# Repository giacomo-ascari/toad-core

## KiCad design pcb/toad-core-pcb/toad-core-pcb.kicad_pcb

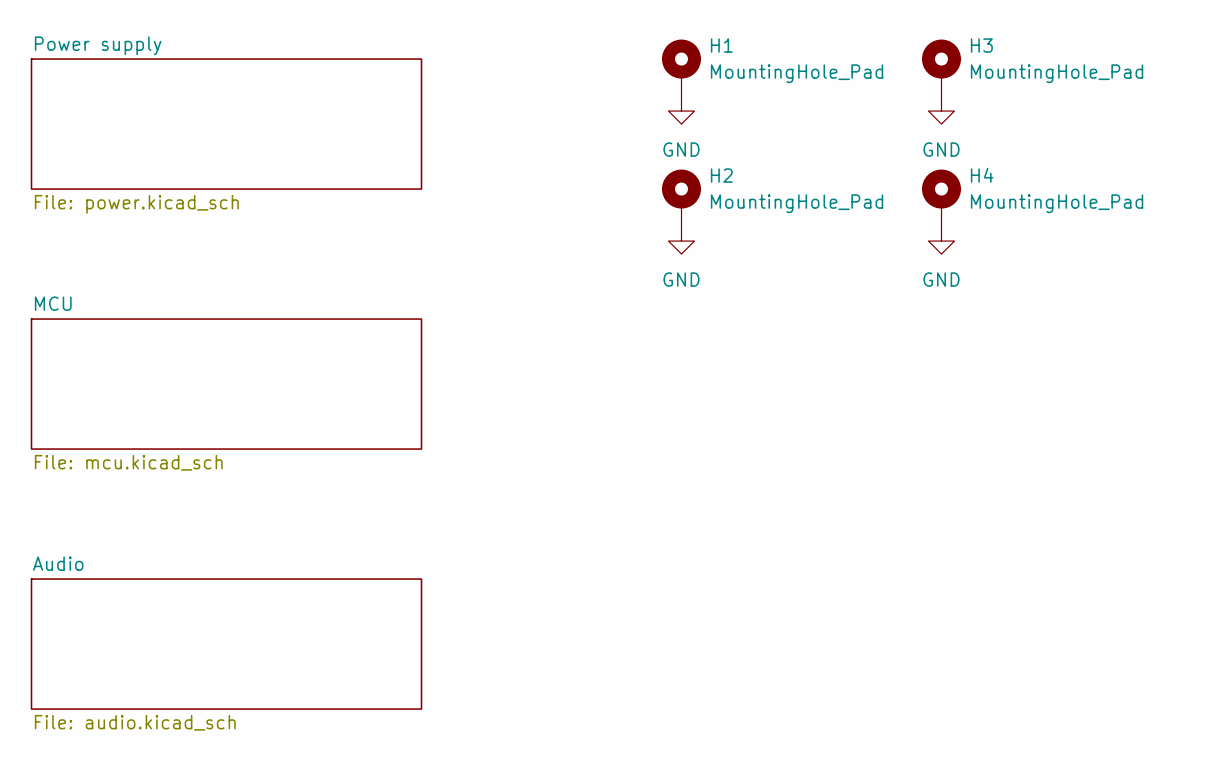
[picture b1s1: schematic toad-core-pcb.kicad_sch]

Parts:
H1, H2, H3, H4: MountingHole_Pad; MountingHole_3.2mm_M3_ISO14580_Pad

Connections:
GND: H1.1 (1_1), H2.1 (1_1), H3.1 (1_1), H4.1 (1_1); also elsewhere on the board

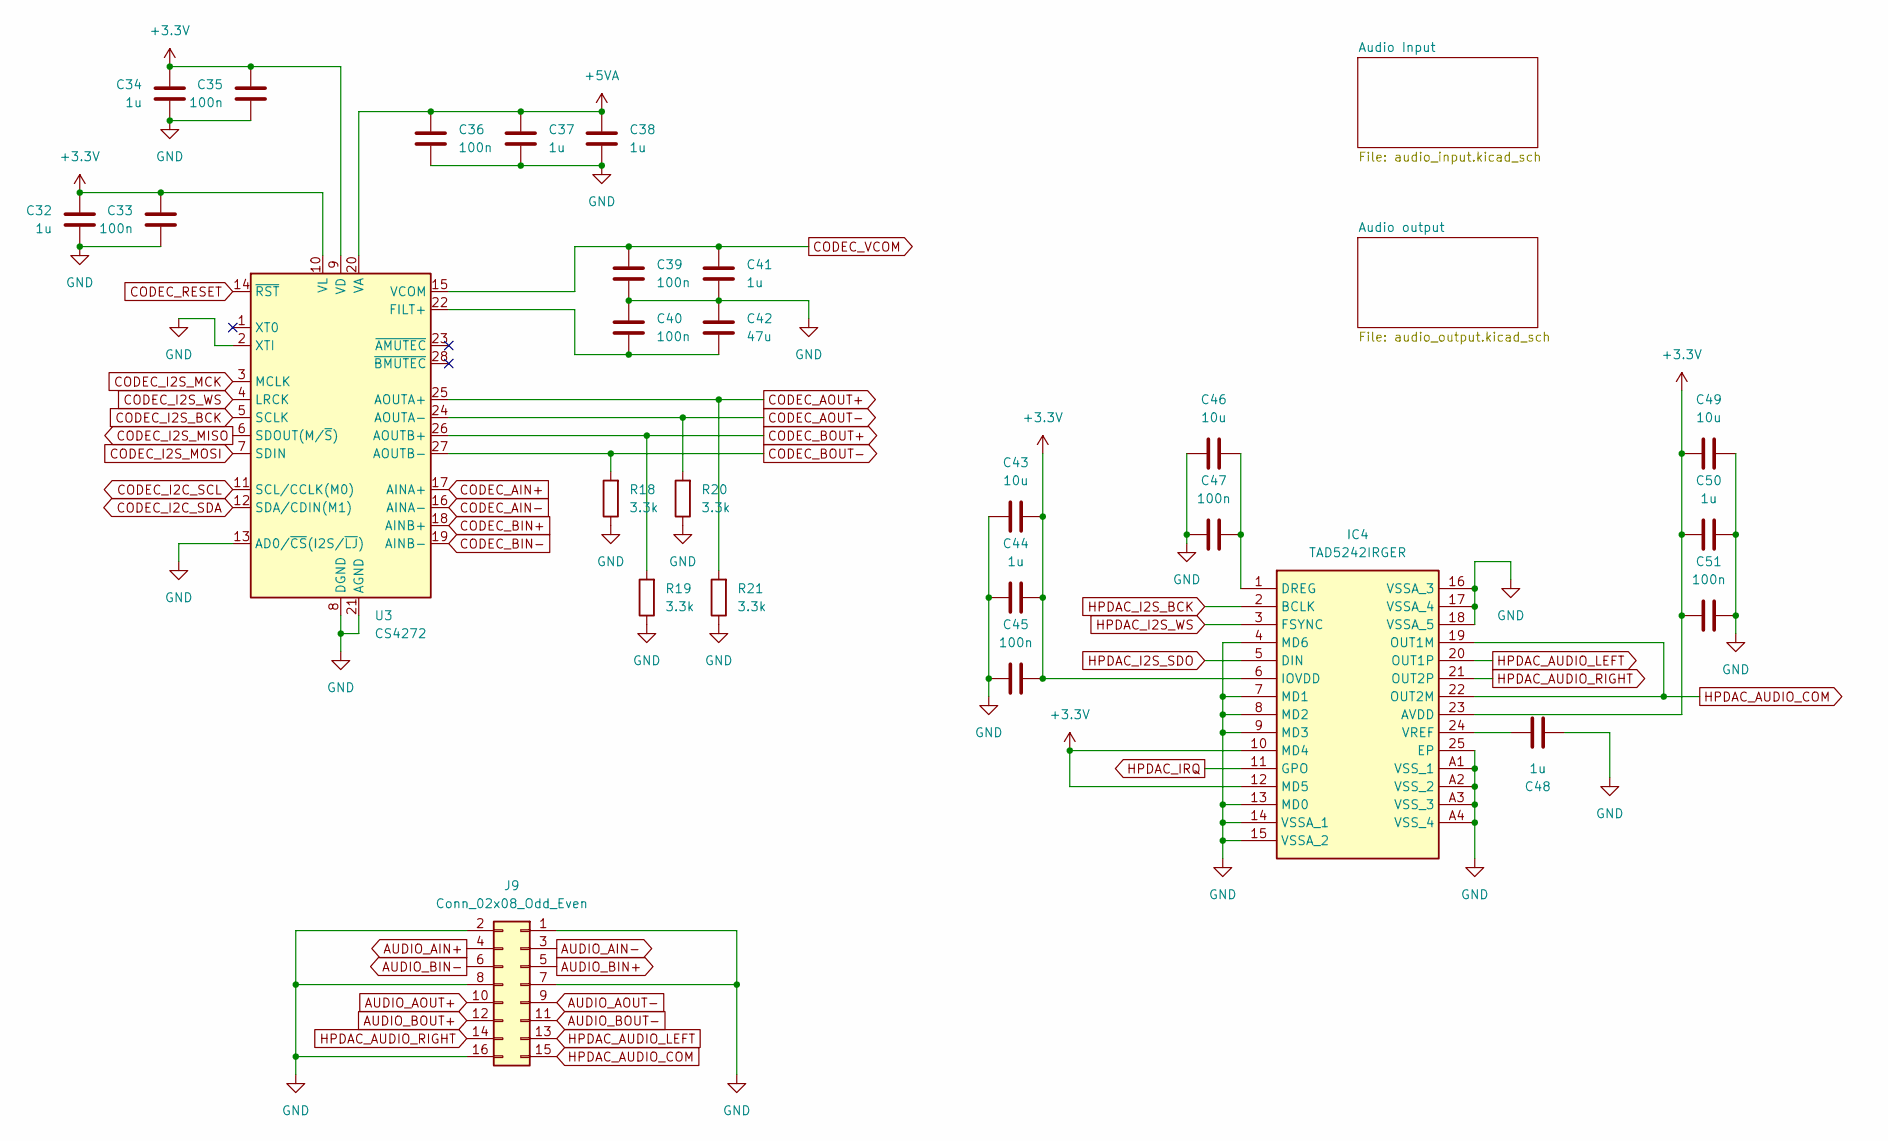
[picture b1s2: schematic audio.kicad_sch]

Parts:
C32, C34, C37, C38, C41, C44, C48, C50: 1u; C_0603_1608Metric
C33, C35, C36, C39, C40, C45, C47, C51: 100n; C_0603_1608Metric
C42: 47u; C_0805_2012Metric
C43, C46, C49: 10u; C_0805_2012Metric
IC4: TAD5242IRGER; Manufacturer_Part_Number TAD5242IRGER; Mouser Part Number 595-TAD5242IRGER
J9: Conn_02x08_Odd_Even; PinHeader_2x08_P2.54mm_Vertical
R18, R19, R20, R21: 3.3k; R_0603_1608Metric
U3: CS4272; TSSOP-28_4.4x9.7mm_P0.65mm

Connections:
+3.3V: C32.1, C33.1, C34.1, C35.1, C43.1, C44.1, C45.1, C49.1, C50.1, C51.1, IC4.6 (IOVDD), IC4.10 (MD4), IC4.12 (MD5), IC4.23 (AVDD), U3.9 (VD), U3.10 (VL); also elsewhere on the board
+5VA: C36.1, C37.1, C38.1, U3.20 (VA); also elsewhere on the board
AUDIO_AIN+: J9.4; also elsewhere on the board
AUDIO_AIN-: J9.3; also elsewhere on the board
AUDIO_AOUT+: J9.10; also elsewhere on the board
AUDIO_AOUT-: J9.9; also elsewhere on the board
AUDIO_BIN+: J9.5; also elsewhere on the board
AUDIO_BIN-: J9.6; also elsewhere on the board
AUDIO_BOUT+: J9.12; also elsewhere on the board
AUDIO_BOUT-: J9.11; also elsewhere on the board
CODEC_AIN+: U3.17 (AINA+); also elsewhere on the board
CODEC_AIN-: U3.16 (AINA-); also elsewhere on the board
CODEC_AOUT+: R21.2, U3.25 (AOUTA+); also elsewhere on the board
CODEC_AOUT-: R20.2, U3.24 (AOUTA-); also elsewhere on the board
CODEC_BIN+: U3.18 (AINB+); also elsewhere on the board
CODEC_BIN-: U3.19 (AINB-); also elsewhere on the board
CODEC_BOUT+: R19.2, U3.26 (AOUTB+); also elsewhere on the board
CODEC_BOUT-: R18.2, U3.27 (AOUTB-); also elsewhere on the board
CODEC_I2C_SCL: U3.11 (SCL/CCLK(M0)); also elsewhere on the board
CODEC_I2C_SDA: U3.12 (SDA/CDIN(M1)); also elsewhere on the board
CODEC_I2S_BCK: U3.5 (SCLK); also elsewhere on the board
CODEC_I2S_MCK: U3.3 (MCLK); also elsewhere on the board
CODEC_I2S_MISO: U3.6 (SDOUT(M/~S)); also elsewhere on the board
CODEC_I2S_MOSI: U3.7 (SDIN); also elsewhere on the board
CODEC_I2S_WS: U3.4 (LRCK); also elsewhere on the board
CODEC_RESET: U3.14 (~RST); also elsewhere on the board
CODEC_VCOM: C39.1, C41.1, U3.15 (VCOM); also elsewhere on the board
GND: C32.2, C33.2, C34.2, C35.2, C36.2, C37.2, C38.2, C39.2, C40.1, C41.2, C42.1, C43.2, C44.2, C45.2, C46.2, C47.2, C48.1, C49.2, C50.2, C51.2, IC4.4 (MD6), IC4.7 (MD1), IC4.8 (MD2), IC4.9 (MD3), IC4.13 (MD0), IC4.14 (VSSA_1), IC4.15 (VSSA_2), IC4.16 (VSSA_3), IC4.17 (VSSA_4), IC4.18 (VSSA_5), IC4.25 (EP), IC4.A1 (VSS_1), IC4.A2 (VSS_2), IC4.A3 (VSS_3), IC4.A4 (VSS_4), J9.1, J9.2, J9.7, J9.8, J9.16, R18.1, R19.1, R20.1, R21.1, U3.2 (XTI), U3.8 (DGND), U3.13 (AD0/~CS(I2S/~LJ)), U3.21 (AGND); also elsewhere on the board
HPDAC_AUDIO_COM: IC4.19 (OUT1M), IC4.22 (OUT2M), J9.15
HPDAC_AUDIO_LEFT: IC4.20 (OUT1P), J9.13
HPDAC_AUDIO_RIGHT: IC4.21 (OUT2P), J9.14
HPDAC_I2S_BCK: IC4.2 (BCLK); also elsewhere on the board
HPDAC_I2S_SDO: IC4.5 (DIN); also elsewhere on the board
HPDAC_I2S_WS: IC4.3 (FSYNC); also elsewhere on the board
HPDAC_IRQ: IC4.11 (GPO); also elsewhere on the board
unnamed: C46.1, C47.1, IC4.1 (DREG)
unnamed: C48.2, IC4.24 (VREF)
unnamed: C40.2, C42.2, U3.22 (FILT+)

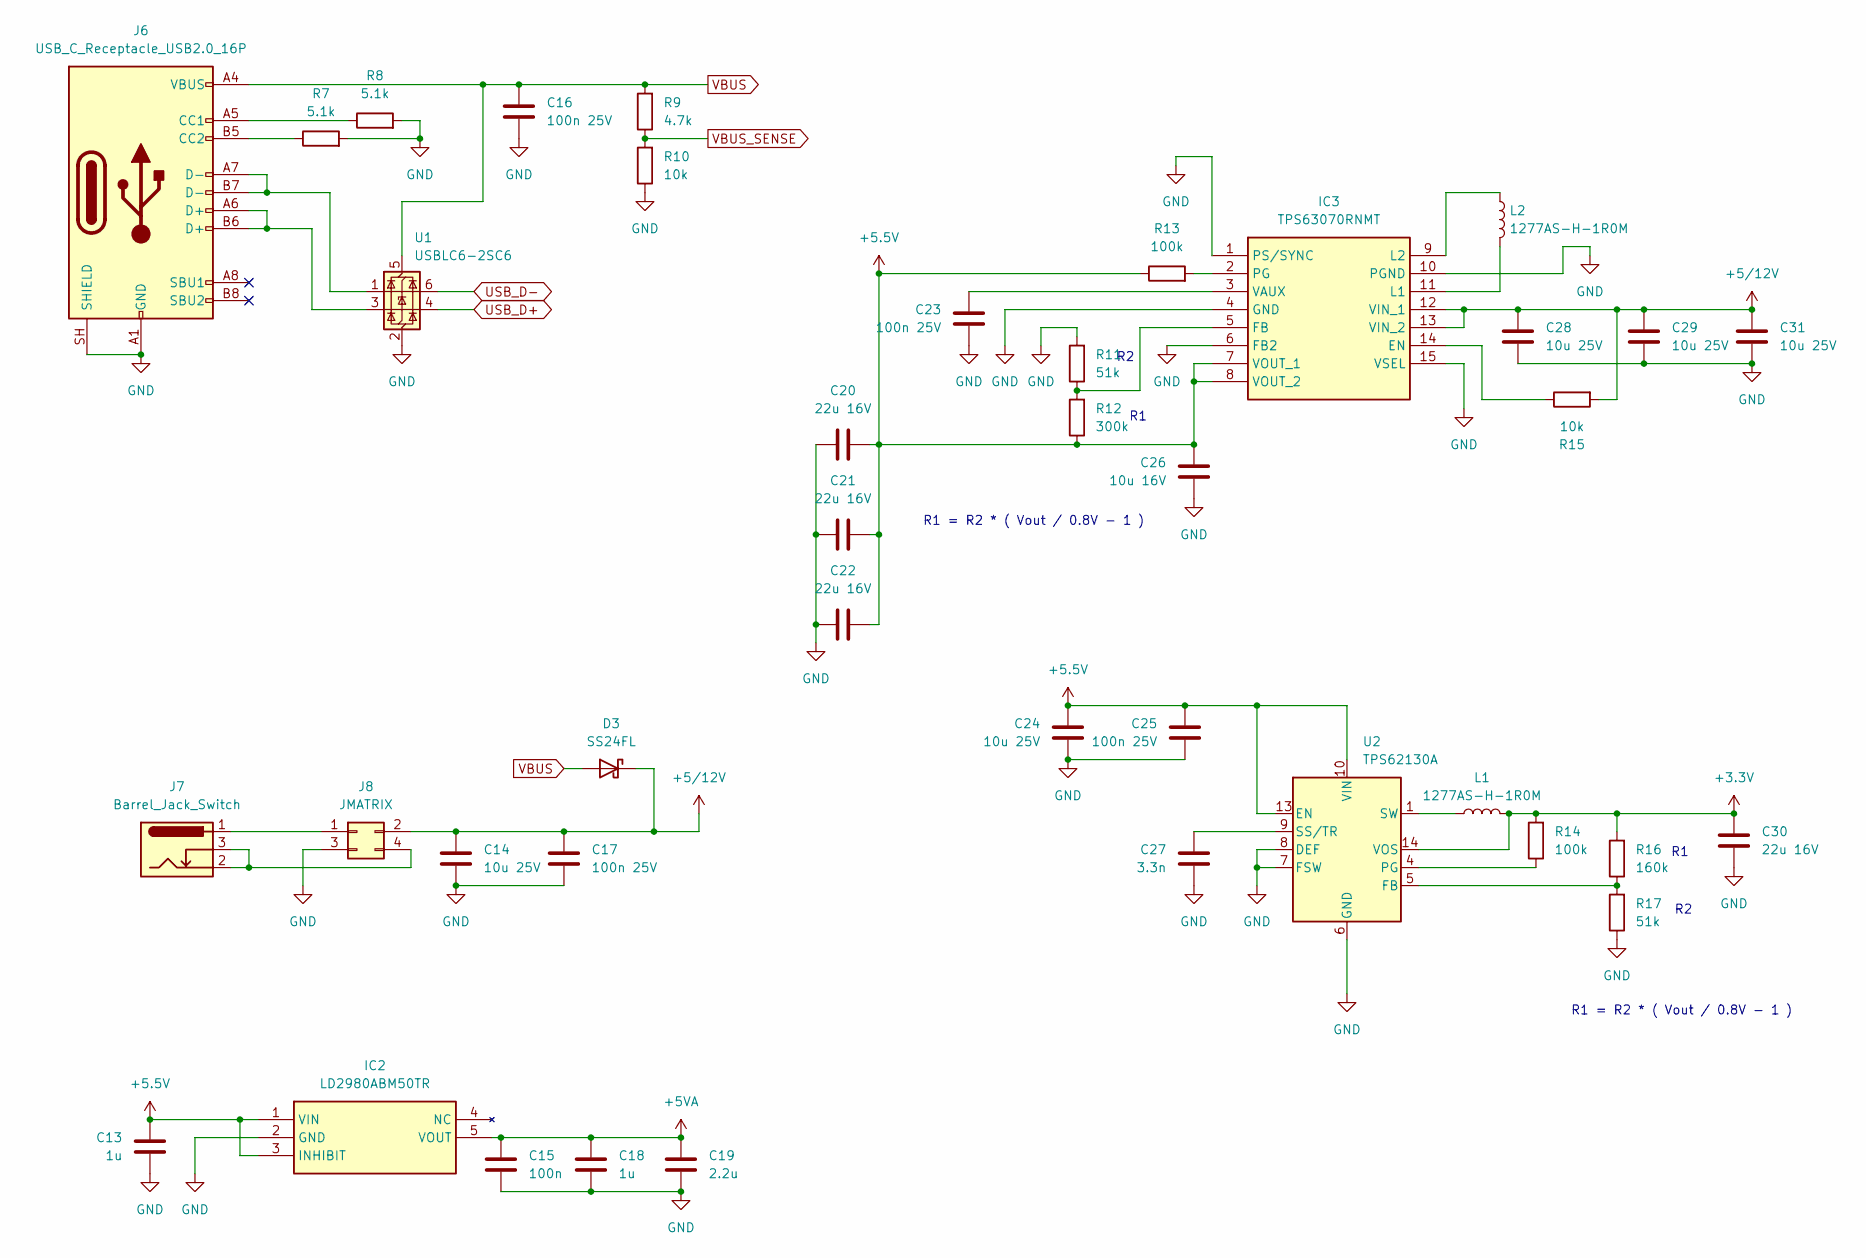
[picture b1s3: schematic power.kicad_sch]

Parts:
C13, C18: 1u; C_0603_1608Metric
C14, C24, C29, C31: 10u 25V; C_0805_2012Metric
C15: 100n; C_0603_1608Metric
C16, C17, C23, C25: 100n 25V; C_0603_1608Metric
C19: 2.2u; C_0603_1608Metric
C20, C21, C22, C30: 22u 16V; C_0805_2012Metric
C26: 10u 16V; C_0603_1608Metric
C27: 3.3n; C_0603_1608Metric
C28: 10u 25V; C_0603_1608Metric
D3: SS24FL; D_SOD-123F
IC2: LD2980ABM50TR; SOT95P280X145-5N; Manufacturer_Part_Number LD2980ABM50TR; Mouser Part Number 511-LD2980ABM50
IC3: TPS63070RNMT; TPS630701RNMR; Manufacturer_Part_Number TPS63070RNMT; Mouser Part Number 595-TPS63070RNMT
J6: USB_C_Receptacle_USB2.0_16P; USB_C_Receptacle_GCT_USB4105-xx-A_16P_TopMnt_Horizontal
J7: Barrel_Jack_Switch; BarrelJack_Wuerth_6941xx301002
J8: JMATRIX; PinHeader_2x02_P2.54mm_Vertical
L1, L2: 1277AS-H-1R0M; L_1210_3225Metric
R7, R8: 5.1k; R_0603_1608Metric
R9: 4.7k; R_0603_1608Metric
R10, R15: 10k; R_0603_1608Metric
R11, R17: 51k; R_0603_1608Metric
R12: 300k; R_0603_1608Metric
R13, R14: 100k; R_0603_1608Metric
R16: 160k; R_0603_1608Metric
U1: USBLC6-2SC6; SOT-23-6
U2: TPS62130A; VQFN-16-1EP_3x3mm_P0.5mm_EP1.68x1.68mm_ThermalVias

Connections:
+3.3V: C30.1, L1.2, R14.2, R16.2, U2.14 (VOS); also elsewhere on the board
+5.5V: C13.1, C20.2, C21.2, C22.2, C24.1, C25.1, C26.1, IC2.1 (VIN), IC2.3 (INHIBIT), IC3.7 (VOUT_1), IC3.8 (VOUT_2), R12.1, R13.1, U2.10 (VIN), U2.11 (VIN), U2.12 (VIN), U2.13 (EN)
+5VA: C15.1, C18.1, C19.1, IC2.5 (VOUT); also elsewhere on the board
+5/12V: C14.1, C17.1, C28.1, C29.1, C31.1, D3.1 (K), IC3.12 (VIN_1), IC3.13 (VIN_2), J8.2, R15.2
GND: C13.2, C14.2, C15.2, C16.2, C17.2, C18.2, C19.2, C20.1, C21.1, C22.1, C23.2, C24.2, C25.2, C26.2, C27.2, C28.2, C29.2, C30.2, C31.2, IC2.2 (GND), IC3.1 (PS/SYNC), IC3.4 (GND), IC3.6 (FB2), IC3.10 (PGND), IC3.15 (VSEL), J6.A1 (GND), J6.A12 (GND), J6.B1 (GND), J6.B12 (GND), J6.SH (SHIELD), J8.3, R7.2, R8.2, R10.1, R11.2, R17.1, U1.2 (GND), U2.6 (GND), U2.7 (FSW), U2.8 (DEF), U2.15 (GND), U2.16 (GND), U2.17 (GND); also elsewhere on the board
unnamed: IC3.14 (EN), R15.1
unnamed: IC3.5 (FB), R11.1, R12.2
unnamed: IC3.11 (L1), L2.2
unnamed: IC3.9 (L2), L2.1
unnamed: IC3.2 (PG), R13.2
unnamed: C23.1, IC3.3 (VAUX)
unnamed: J6.A5 (CC1), R8.1
unnamed: J6.B5 (CC2), R7.1
unnamed: J6.A6 (D+), J6.B6 (D+), U1.3 (I/O2)
unnamed: J6.A7 (D-), J6.B7 (D-), U1.1 (I/O1)
unnamed: J7.1, J8.1
unnamed: J7.2, J7.3, J8.4
unnamed: L1.1, U2.1 (SW), U2.2 (SW), U2.3 (SW)
unnamed: R16.1, R17.2, U2.5 (FB)
unnamed: R14.1, U2.4 (PG)
unnamed: C27.1, U2.9 (SS/TR)
USB_D+: U1.4 (I/O2); also elsewhere on the board
USB_D-: U1.6 (I/O1); also elsewhere on the board
VBUS: C16.1, D3.2 (A), J6.A4 (VBUS), J6.A9 (VBUS), J6.B4 (VBUS), J6.B9 (VBUS), R9.2, U1.5 (VBUS)
VBUS_SENSE: R9.1, R10.2; also elsewhere on the board

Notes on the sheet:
R1 = R2 * ( Vout / 0.8V - 1 )

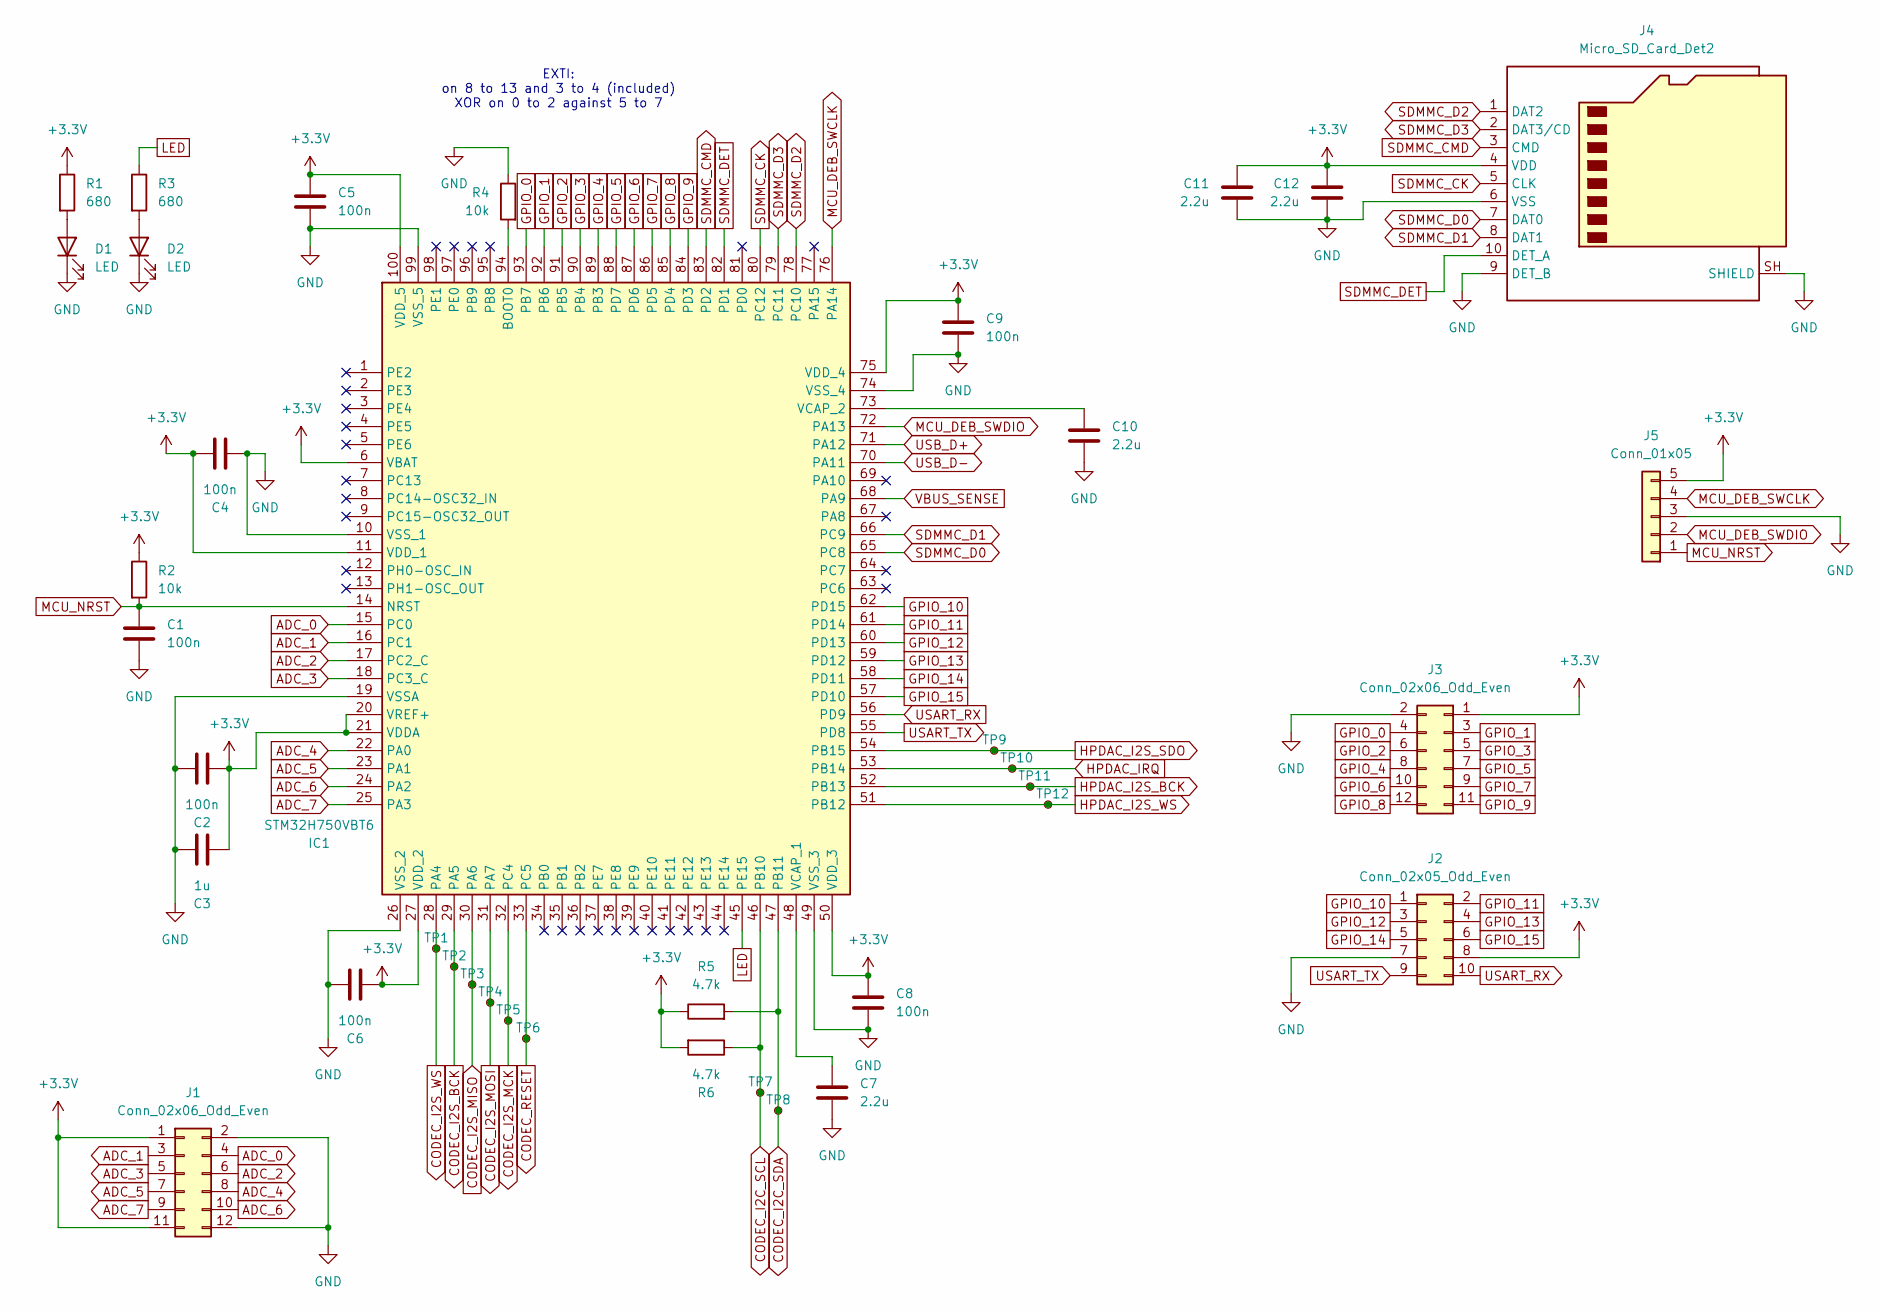
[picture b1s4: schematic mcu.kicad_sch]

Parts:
C1, C2, C4, C5, C6, C8, C9: 100n; C_0603_1608Metric
C3: 1u; C_0603_1608Metric
C7, C10, C11, C12: 2.2u; C_0603_1608Metric
D1, D2: LED; LED_0603_1608Metric
IC1: STM32H750VBT6; QFP50P1600X1600X160-100N; Manufacturer_Part_Number STM32H750VBT6; Mouser Part Number 511-STM32H750VBT6
J1, J3: Conn_02x06_Odd_Even; PinHeader_2x06_P2.54mm_Vertical
J2: Conn_02x05_Odd_Even; PinHeader_2x05_P2.54mm_Vertical
J4: Micro_SD_Card_Det2; microSD_HC_Molex_104031-0811
J5: Conn_01x05; JST_PH_B5B-PH-K_1x05_P2.00mm_Vertical
R1, R3: 680; R_0603_1608Metric
R2, R4: 10k; R_0603_1608Metric
R5, R6: 4.7k; R_0603_1608Metric
TP1, TP2, TP3, TP4, TP5, TP6, TP7, TP8, TP9, TP10, TP11, TP12: TestPoint_Small; custom_d0.6

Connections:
+3.3V: C2.1, C3.1, C4.2, C5.1, C6.1, C8.1, C9.1, C11.1, C12.1, IC1.6 (VBAT), IC1.11 (VDD_1), IC1.20 (VREF+), IC1.21 (VDDA), IC1.27 (VDD_2), IC1.50 (VDD_3), IC1.75 (VDD_4), IC1.100 (VDD_5), J1.1, J1.11, J2.8, J3.1, J4.4 (VDD), J5.5, R1.1, R2.1, R5.1, R6.2; also elsewhere on the board
ADC_0: IC1.15 (PC0), J1.4
ADC_1: IC1.16 (PC1), J1.3
ADC_2: IC1.17 (PC2_C), J1.6
ADC_3: IC1.18 (PC3_C), J1.5
ADC_4: IC1.22 (PA0), J1.8
ADC_5: IC1.23 (PA1), J1.7
ADC_6: IC1.24 (PA2), J1.10
ADC_7: IC1.25 (PA3), J1.9
CODEC_I2C_SCL: IC1.46 (PB10), R6.1, TP7.1 (1_1); also elsewhere on the board
CODEC_I2C_SDA: IC1.47 (PB11), R5.2, TP8.1 (1_1); also elsewhere on the board
CODEC_I2S_BCK: IC1.29 (PA5), TP2.1 (1_1); also elsewhere on the board
CODEC_I2S_MCK: IC1.32 (PC4), TP5.1 (1_1); also elsewhere on the board
CODEC_I2S_MISO: IC1.30 (PA6), TP3.1 (1_1); also elsewhere on the board
CODEC_I2S_MOSI: IC1.31 (PA7), TP4.1 (1_1); also elsewhere on the board
CODEC_I2S_WS: IC1.28 (PA4), TP1.1 (1_1); also elsewhere on the board
CODEC_RESET: IC1.33 (PC5), TP6.1 (1_1); also elsewhere on the board
GND: C1.2, C2.2, C3.2, C4.1, C5.2, C6.2, C7.2, C8.2, C9.2, C10.2, C11.2, C12.2, D1.1 (K), D2.1 (K), IC1.10 (VSS_1), IC1.19 (VSSA), IC1.26 (VSS_2), IC1.49 (VSS_3), IC1.74 (VSS_4), IC1.99 (VSS_5), J1.2, J1.12, J2.7, J3.2, J4.6 (VSS), J4.9 (DET_B), J4.SH (SHIELD), J5.3, R4.1; also elsewhere on the board
GPIO_0: IC1.93 (PB7), J3.4
GPIO_1: IC1.92 (PB6), J3.3
GPIO_2: IC1.91 (PB5), J3.6
GPIO_3: IC1.90 (PB4), J3.5
GPIO_4: IC1.89 (PB3), J3.8
GPIO_5: IC1.88 (PD7), J3.7
GPIO_6: IC1.87 (PD6), J3.10
GPIO_7: IC1.86 (PD5), J3.9
GPIO_8: IC1.85 (PD4), J3.12
GPIO_9: IC1.84 (PD3), J3.11
GPIO_10: IC1.62 (PD15), J2.1
GPIO_11: IC1.61 (PD14), J2.2
GPIO_12: IC1.60 (PD13), J2.3
GPIO_13: IC1.59 (PD12), J2.4
GPIO_14: IC1.58 (PD11), J2.5
GPIO_15: IC1.57 (PD10), J2.6
HPDAC_I2S_BCK: IC1.52 (PB13), TP11.1 (1_1); also elsewhere on the board
HPDAC_I2S_SDO: IC1.54 (PB15), TP9.1 (1_1); also elsewhere on the board
HPDAC_I2S_WS: IC1.51 (PB12), TP12.1 (1_1); also elsewhere on the board
HPDAC_IRQ: IC1.53 (PB14), TP10.1 (1_1); also elsewhere on the board
LED: IC1.45 (PE15), R3.1
MCU_DEB_SWCLK: IC1.76 (PA14), J5.4
MCU_DEB_SWDIO: IC1.72 (PA13), J5.2
MCU_NRST: C1.1, IC1.14 (NRST), J5.1, R2.2
unnamed: D1.2 (A), R1.2
unnamed: D2.2 (A), R3.2
unnamed: IC1.94 (BOOT0), R4.2
unnamed: C7.1, IC1.48 (VCAP_1)
unnamed: C10.1, IC1.73 (VCAP_2)
SDMMC_CK: IC1.80 (PC12), J4.5 (CLK)
SDMMC_CMD: IC1.83 (PD2), J4.3 (CMD)
SDMMC_D0: IC1.65 (PC8), J4.7 (DAT0)
SDMMC_D1: IC1.66 (PC9), J4.8 (DAT1)
SDMMC_D2: IC1.78 (PC10), J4.1 (DAT2)
SDMMC_D3: IC1.79 (PC11), J4.2 (DAT3/CD)
SDMMC_DET: IC1.82 (PD1), J4.10 (DET_A)
USART_RX: IC1.56 (PD9), J2.10
USART_TX: IC1.55 (PD8), J2.9
USB_D+: IC1.71 (PA12); also elsewhere on the board
USB_D-: IC1.70 (PA11); also elsewhere on the board
VBUS_SENSE: IC1.68 (PA9); also elsewhere on the board

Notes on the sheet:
EXTI: on 8 to 13 and 3 to 4 (included) XOR on 0 to 2 against 5 to 7

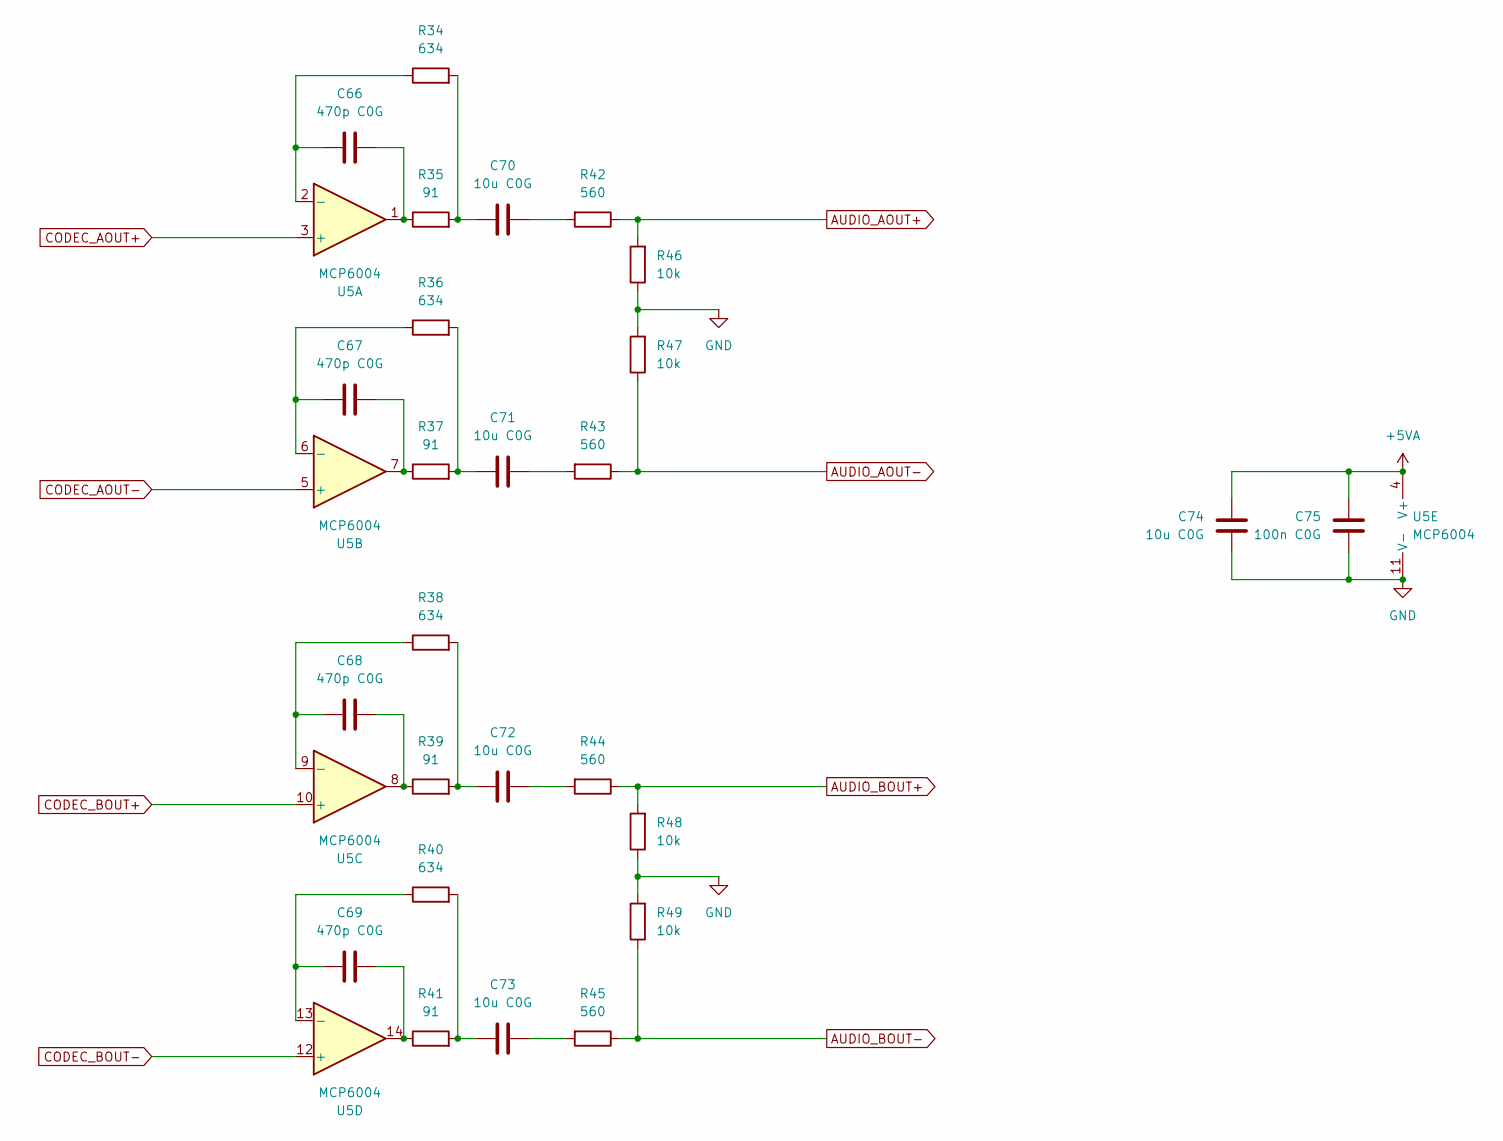
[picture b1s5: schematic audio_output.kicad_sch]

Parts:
C66, C67, C68, C69: 470p C0G; C_0603_1608Metric
C70, C71, C72, C73, C74: 10u C0G; C_0805_2012Metric
C75: 100n C0G; C_0603_1608Metric
R34, R36, R38, R40: 634; R_0603_1608Metric
R35, R37, R39, R41: 91; R_0603_1608Metric
R42, R43, R44, R45: 560; R_0603_1608Metric
R46, R47, R48, R49: 10k; R_0603_1608Metric
U5: MCP6004; TSSOP-14_4.4x5mm_P0.65mm

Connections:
+5VA: C74.1, C75.1, U5.4 (V+); also elsewhere on the board
AUDIO_AOUT+: R42.1, R46.2; also elsewhere on the board
AUDIO_AOUT-: R43.1, R47.1; also elsewhere on the board
AUDIO_BOUT+: R44.1, R48.2; also elsewhere on the board
AUDIO_BOUT-: R45.1, R49.1; also elsewhere on the board
CODEC_AOUT+: U5.3 (+); also elsewhere on the board
CODEC_AOUT-: U5.5 (+); also elsewhere on the board
CODEC_BOUT+: U5.10 (+); also elsewhere on the board
CODEC_BOUT-: U5.12 (+); also elsewhere on the board
GND: C74.2, C75.2, R46.1, R47.2, R48.1, R49.2, U5.11 (V-); also elsewhere on the board
unnamed: C66.1, R35.1, U5.1
unnamed: C67.1, R37.1, U5.7
unnamed: C68.1, R39.1, U5.8
unnamed: C69.1, R41.1, U5.14
unnamed: C70.1, R42.2
unnamed: C70.2, R34.2, R35.2
unnamed: C71.1, R43.2
unnamed: C71.2, R36.2, R37.2
unnamed: C72.1, R44.2
unnamed: C72.2, R38.2, R39.2
unnamed: C73.1, R45.2
unnamed: C73.2, R40.2, R41.2
unnamed: C66.2, R34.1, U5.2 (-)
unnamed: C67.2, R36.1, U5.6 (-)
unnamed: C68.2, R38.1, U5.9 (-)
unnamed: C69.2, R40.1, U5.13 (-)

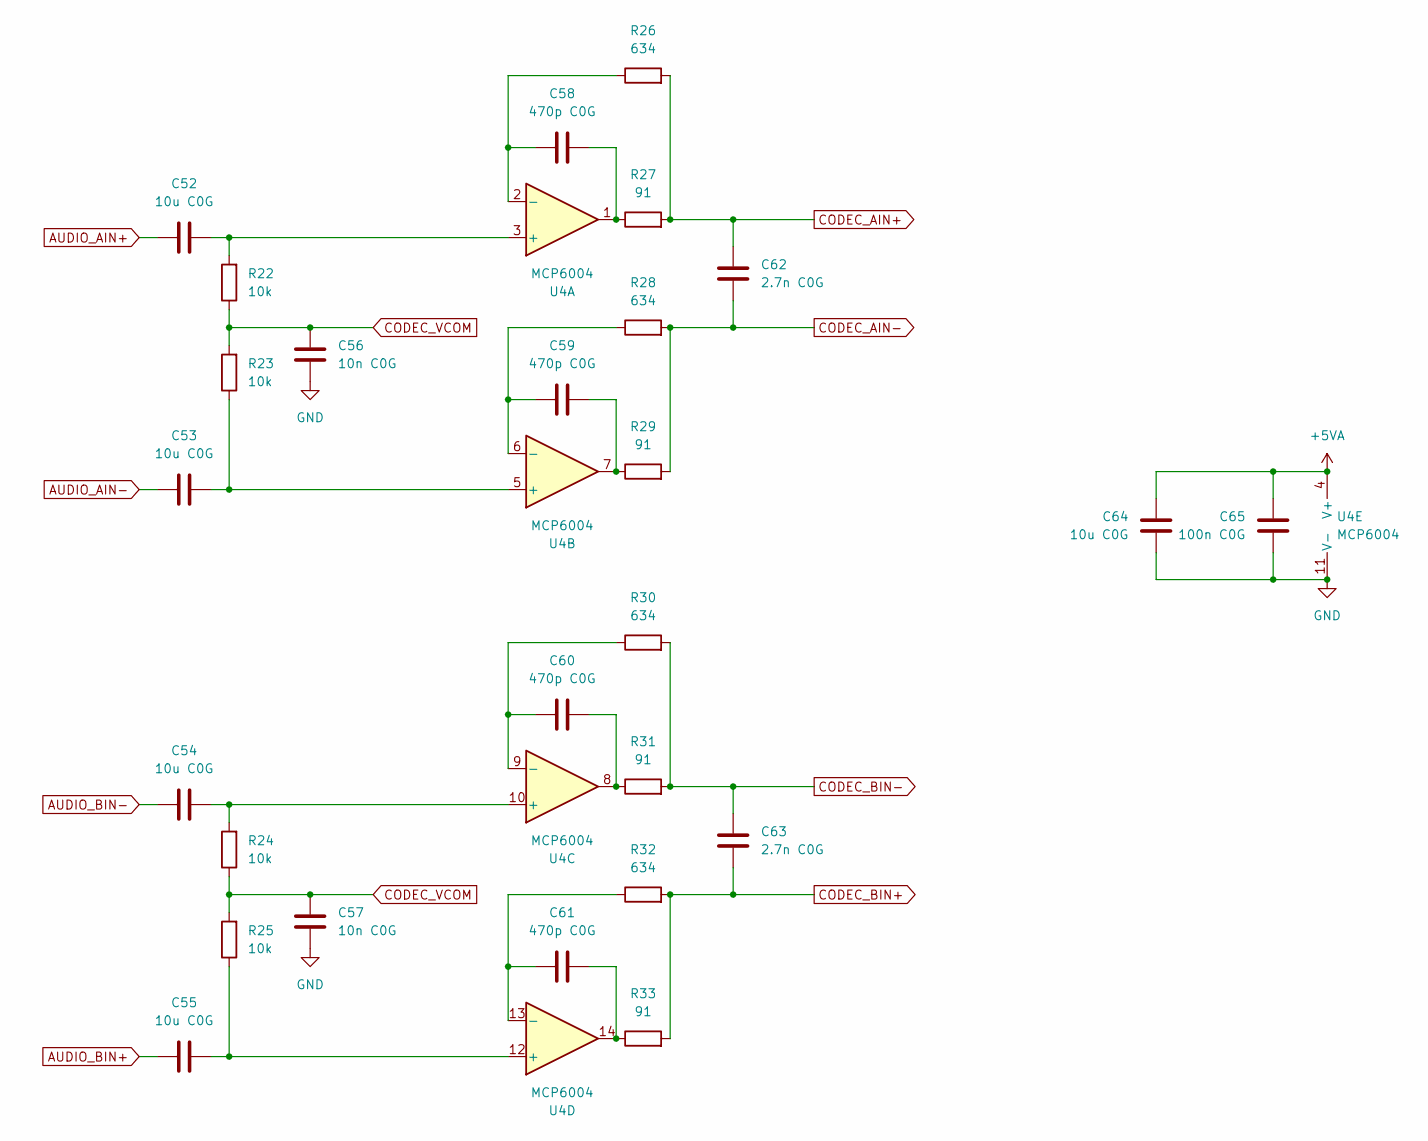
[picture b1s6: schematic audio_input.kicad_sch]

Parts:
C52, C53, C54, C55, C64: 10u C0G; C_0805_2012Metric
C56, C57: 10n C0G; C_0603_1608Metric
C58, C59, C60, C61: 470p C0G; C_0603_1608Metric
C62, C63: 2.7n C0G; C_0603_1608Metric
C65: 100n C0G; C_0603_1608Metric
R22, R23, R24, R25: 10k; R_0603_1608Metric
R26, R28, R30, R32: 634; R_0603_1608Metric
R27, R29, R31, R33: 91; R_0603_1608Metric
U4: MCP6004; TSSOP-14_4.4x5mm_P0.65mm

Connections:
+5VA: C64.1, C65.1, U4.4 (V+); also elsewhere on the board
AUDIO_AIN+: C52.2; also elsewhere on the board
AUDIO_AIN-: C53.2; also elsewhere on the board
AUDIO_BIN+: C55.2; also elsewhere on the board
AUDIO_BIN-: C54.2; also elsewhere on the board
CODEC_AIN+: C62.1, R26.2, R27.2; also elsewhere on the board
CODEC_AIN-: C62.2, R28.2, R29.2; also elsewhere on the board
CODEC_BIN+: C63.2, R32.2, R33.2; also elsewhere on the board
CODEC_BIN-: C63.1, R30.2, R31.2; also elsewhere on the board
CODEC_VCOM: C56.1, C57.1, R22.1, R23.2, R24.1, R25.2; also elsewhere on the board
GND: C56.2, C57.2, C64.2, C65.2, U4.11 (V-); also elsewhere on the board
unnamed: C58.1, R27.1, U4.1
unnamed: C59.1, R29.1, U4.7
unnamed: C60.1, R31.1, U4.8
unnamed: C61.1, R33.1, U4.14
unnamed: C52.1, R22.2, U4.3 (+)
unnamed: C58.2, R26.1, U4.2 (-)
unnamed: C53.1, R23.1, U4.5 (+)
unnamed: C59.2, R28.1, U4.6 (-)
unnamed: C54.1, R24.2, U4.10 (+)
unnamed: C60.2, R30.1, U4.9 (-)
unnamed: C55.1, R25.1, U4.12 (+)
unnamed: C61.2, R32.1, U4.13 (-)

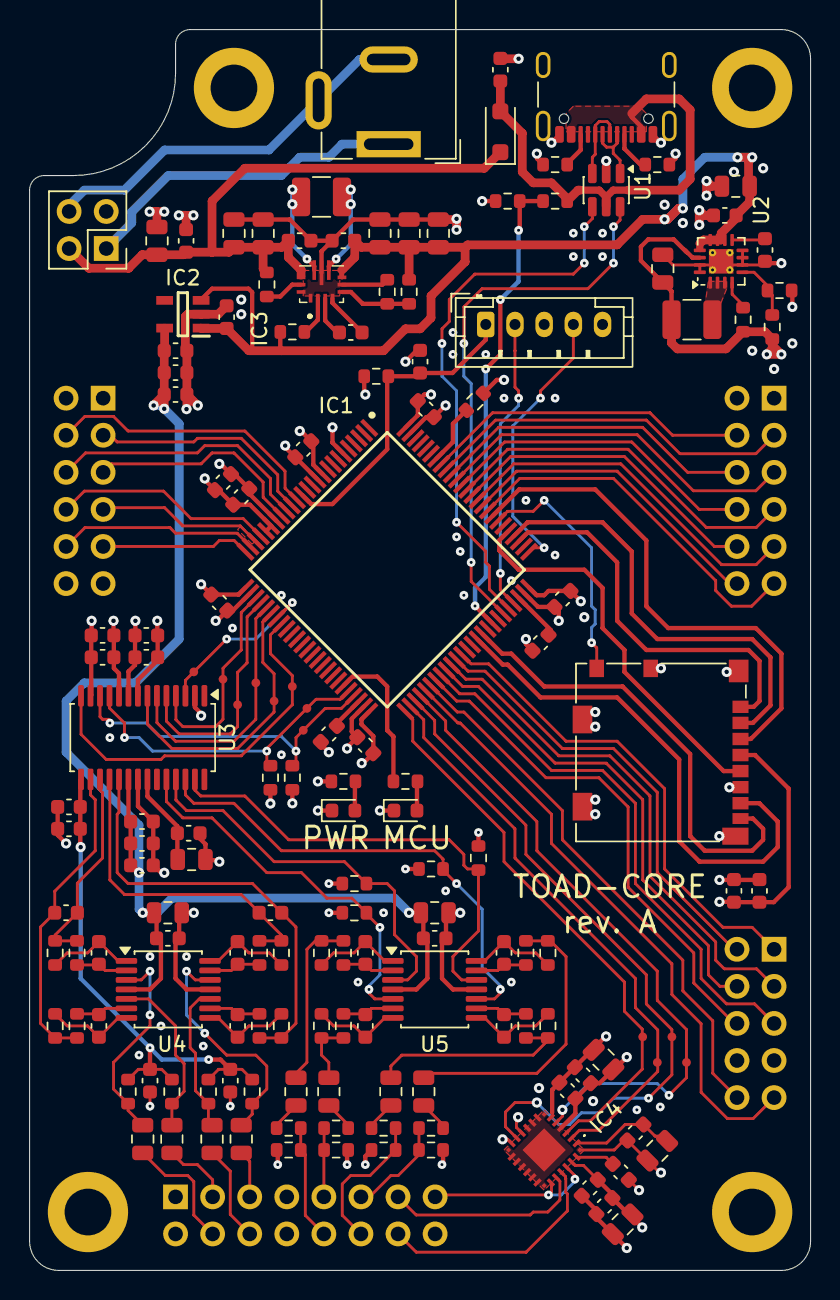
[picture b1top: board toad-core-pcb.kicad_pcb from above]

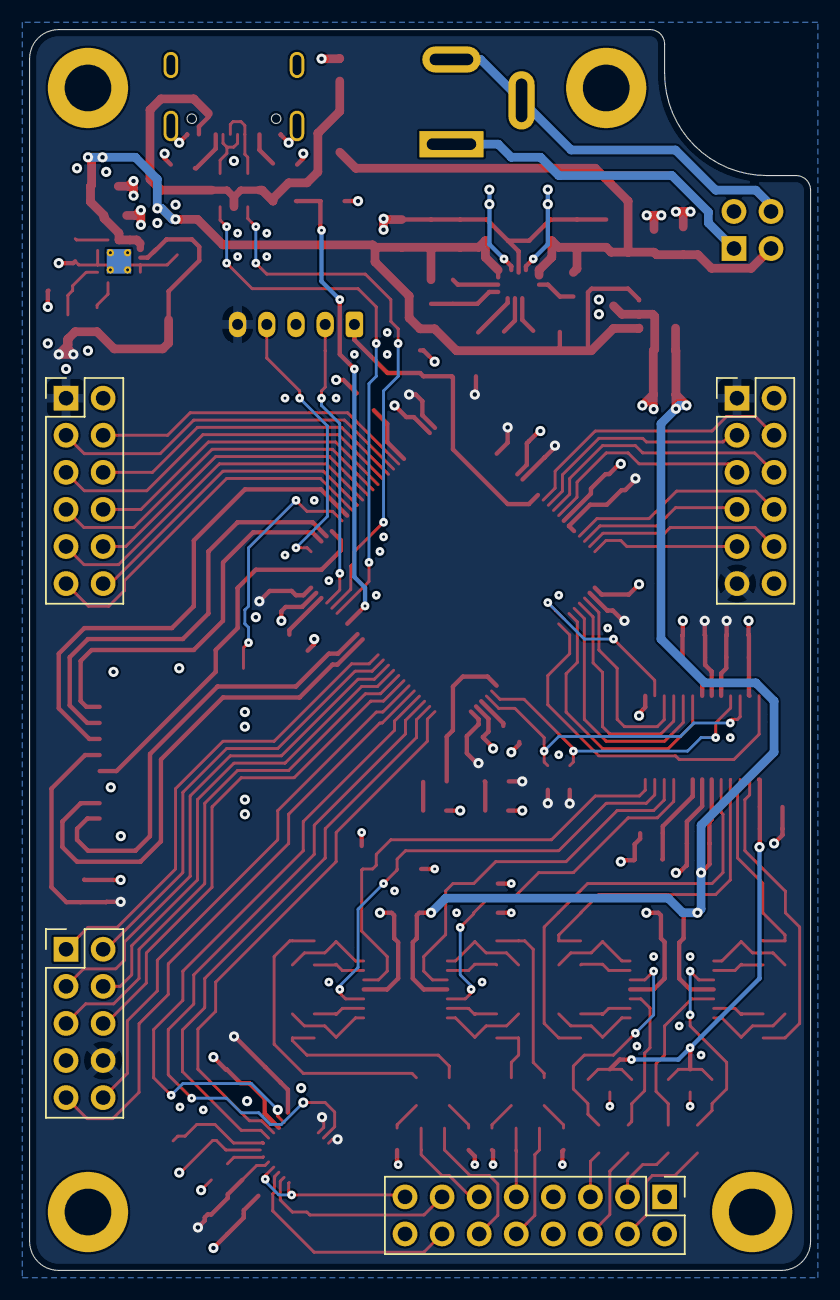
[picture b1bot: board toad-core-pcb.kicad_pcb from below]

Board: 4 copper layers, 53.5 x 85.0 mm, 163 parts (4 on the bottom side), 130 nets.
